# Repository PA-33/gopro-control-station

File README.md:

# GoPro Control Station

A complete remote control station for a GoPro Hero camera.

The system combines a two-axis motorised mount (so the camera can be aimed
without touching it) with full remote control of the camera itself
(shutter, mode, gallery, live HDMI preview). Everything is driven by a
single ESP32-S3 board running closed-loop FOC for the motors, BLE for
the camera commands, and an HTTPS web server for the user interface.

## Features

- Two-axis motorised mount with absolute angular position
- Magnetic encoders for accurate, drift-free positioning
- Soft-limits with automatic end-stop calibration
- Stall protection with auto-recovery (re-centres the motor on re-enable)
- BLE control of the GoPro (shutter, mode, sleep, keep-alive)
- Wi-Fi proxy to the GoPro REST API (gallery, thumbnails, downloads)
- Browser-based live HDMI preview via a USB-C capture card
- Self-signed HTTPS server with embedded certificate
- Persistent configuration and calibration in NVS
- Status LED strip for camera, motors, recording state and battery

The user interacts with the system through two parallel channels:

- **Physical panel** — five buttons (M1+, M1-, M2+, M2-, shutter) and a
  7-LED status strip.
- **Web interface** — served on the station's own Wi-Fi access point:
  control, gallery, live HDMI preview and configuration in a
  mobile-friendly UI.

## Repository layout

```
gopro-control-station/
├── platformio.ini              PlatformIO build configuration
├── README.md
├── LICENSE
│
├── src/                        Firmware sources (Arduino + ESP-IDF)
│   ├── bridge_main.cpp         setup() / loop() / status LEDs
│   ├── bridge_foc.cpp/.h       motor control, buttons, calibration
│   ├── bridge_current.cpp/.h   current sensing + stall detection
│   ├── bridge_ble.cpp/.h       NimBLE client (OpenGoPro)
│   ├── bridge_wifi.cpp/.h      Wi-Fi AP + STA + watchdog
│   ├── bridge_https.cpp/.h     TLS web server + REST proxy
│   ├── bridge_server.cpp/.h    plain HTTP (cert download only)
│   ├── bridge_config.cpp/.h    persistent configuration (NVS)
│   ├── bridge_led.h            LED constants
│   └── ssl_cert.h              embedded TLS certificate (auto-generated)
│
├── data/
│   └── index.html              single-page web UI (served from LittleFS)
│
├── certs/                      TLS certificate + regeneration toolchain
│   ├── bridge_cert.pem
│   ├── bridge_key.pem
│   ├── openssl.cnf
│   ├── generate.bat            Windows: regenerate cert + key + header
│   └── make_header.py          convert PEM into src/ssl_cert.h
│
├── hardware/
│   ├── cad/
│   │   ├── source/             CAD source files
│   │   └── exports/            exported 3D-printable files
│   └── kicad/
│       ├── gimbal_driver_board/ electrical schematic + PCB sources
│       └── exports/            generated manufacturing files
│
└── docs/
    ├── user_manual.pdf           end-user manual
    └── Mode_d_emploi.pdf         end-user manual (French)
```

## Quick start

### 1. Build and flash the firmware

```bash
# Firmware
pio run -e esp32-s3-bridge -t upload

# Web UI (LittleFS image)
pio run -e esp32-s3-bridge -t uploadfs

# Watch the boot log
pio device monitor -e esp32-s3-bridge
```

A clean first boot prints, in order: PCF8574 ready, FOC init OK x2,
Wi-Fi AP up, BLE connected to the camera, HTTPS server started, Wi-Fi
STA connected to the GoPro. See `docs/repport.tex` §5.5 for the
reference serial log.

### 2. Connect

1. Join the Wi-Fi network `GoPro-Bridge` (default password `gopro1234`).
2. Open `https://192.168.4.1` in a browser.
3. Accept the security warning, or download the certificate from the
   *Config* tab and install it to make the warning go away.

### 3. Adapt to your own GoPro

No source edit is required. After the first boot, go to the *Config* tab
in the web UI, replace the GoPro Wi-Fi SSID and password with the ones
printed on your camera (*Connections / Connect Device / GoPro App*),
*Save*, and reboot.

## Documentation

- **`docs/mode_emploi.tex`** — end-user manual (French). Buttons, LEDs,
  web interface, calibration procedure.
- **`hardware/cad/`** — CAD sources and exports for the mechanical
  parts. Print settings and assembly order are documented in §3 of the
  report.
- **`hardware/kicad/`** — full electrical schematic and PCB project. The pin
  assignments are also reproduced in §4 of the report and are
  hard-coded in the firmware (see `src/bridge_foc.cpp`).

## Regenerating the TLS certificate

The repository ships with a self-signed development certificate that
works out of the box. For any deployment where the local network is not
trusted, regenerate it:

```bash
cd certs
generate.bat            # Windows
# POSIX equivalent: see docs/repport.tex Appendix D
```

Then re-flash the firmware. Every client that already trusted the
previous certificate has to install the new one (web UI, *Config* tab).

## Hardware overview

- **MCU**: ESP32-S3 (`esp32-s3-devkitc-1`), 8 MB flash, no PSRAM.
- **Motors**: 2x BLDC (11 pole pairs), each driven by a DRV8313.
- **Encoders**: 2x AS5048A magnetic absolute encoders (SPI / HSPI bus).
- **Buttons**: 5x momentary, multiplexed through a PCF8574T (I2C).
- **Current sense**: 2x INA180A1 with 50 mOhm shunts, read on ADC2.
- **Indicators**: WS2815 strip, 7 LEDs.
- **Camera**: GoPro Hero (any model compatible with the OpenGoPro BLE
  specification) with the official Media Mod for HDMI output.
- **HDMI capture**: any UVC-class USB-C card (UGREEN 15389 is
  auto-selected by the web UI).

## License

This project is released under the [MIT License](LICENSE). You can use,
modify and redistribute it freely, including for commercial purposes,
provided that the copyright notice and the license text are kept.

## Acknowledgements

Built on top of [SimpleFOC](https://docs.simplefoc.com/),
[NimBLE-Arduino](https://github.com/h2zero/NimBLE-Arduino),
[ESPAsyncWebServer](https://github.com/mathieucarbou/ESPAsyncWebServer),
and the [pioarduino fork](https://github.com/pioarduino/platform-espressif32)
of `platform-espressif32`. Camera control follows the
[OpenGoPro](https://gopro.github.io/OpenGoPro/) specification.

## Context

This project was developed by Pierre Adamini and Florian Klein as part of
the Assistive Technology Challenge at EPFL (2026).

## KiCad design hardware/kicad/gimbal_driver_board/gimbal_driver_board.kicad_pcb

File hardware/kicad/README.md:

# KiCad project

Put the full KiCad source project here:

- `*.kicad_pro`
- `*.kicad_sch`
- `*.kicad_pcb`

Optional, only if you create local libraries later:

- `symbols/` for custom symbol libraries
- `footprints/` for custom footprint libraries

Use `exports/` for generated outputs only:

- Gerbers
- drill files
- PDF schematics
- BOM / pick-and-place files

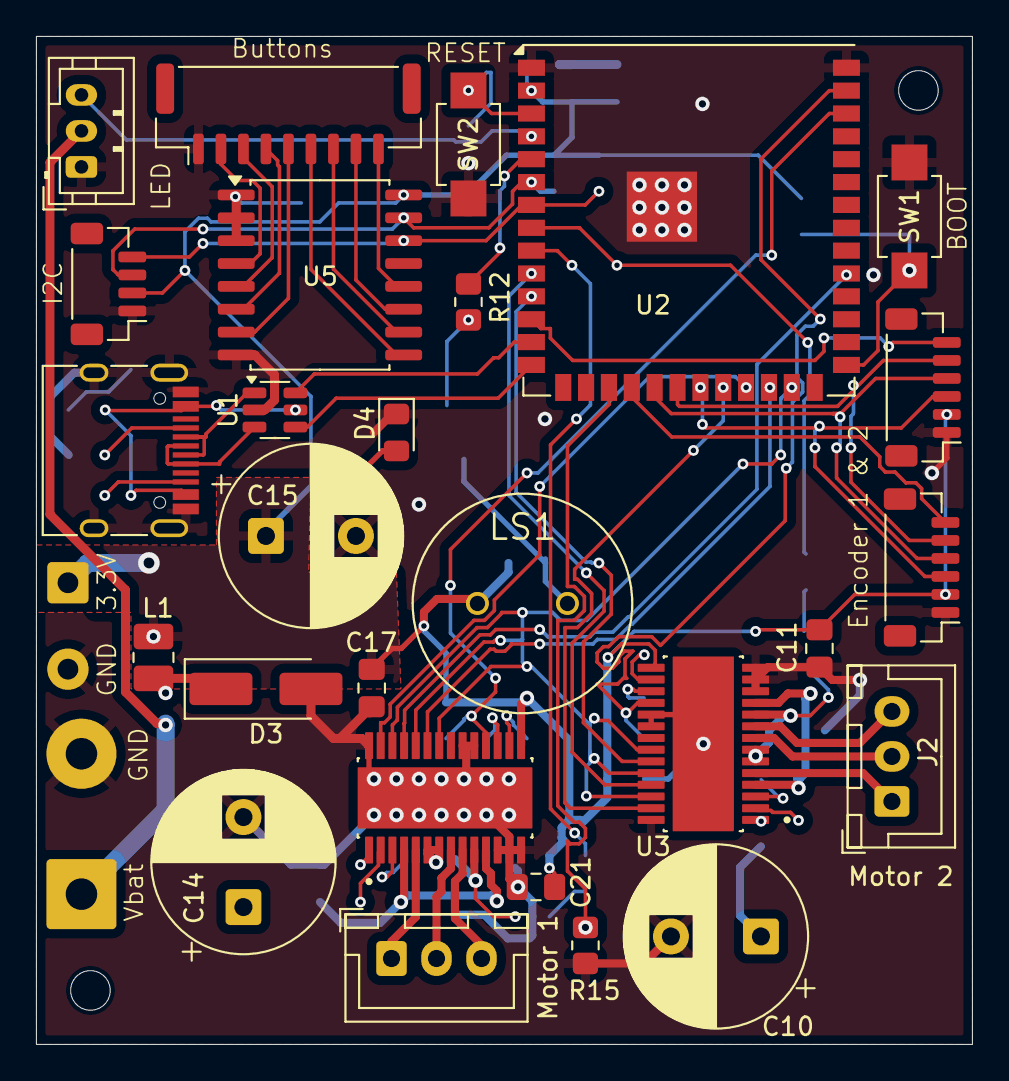
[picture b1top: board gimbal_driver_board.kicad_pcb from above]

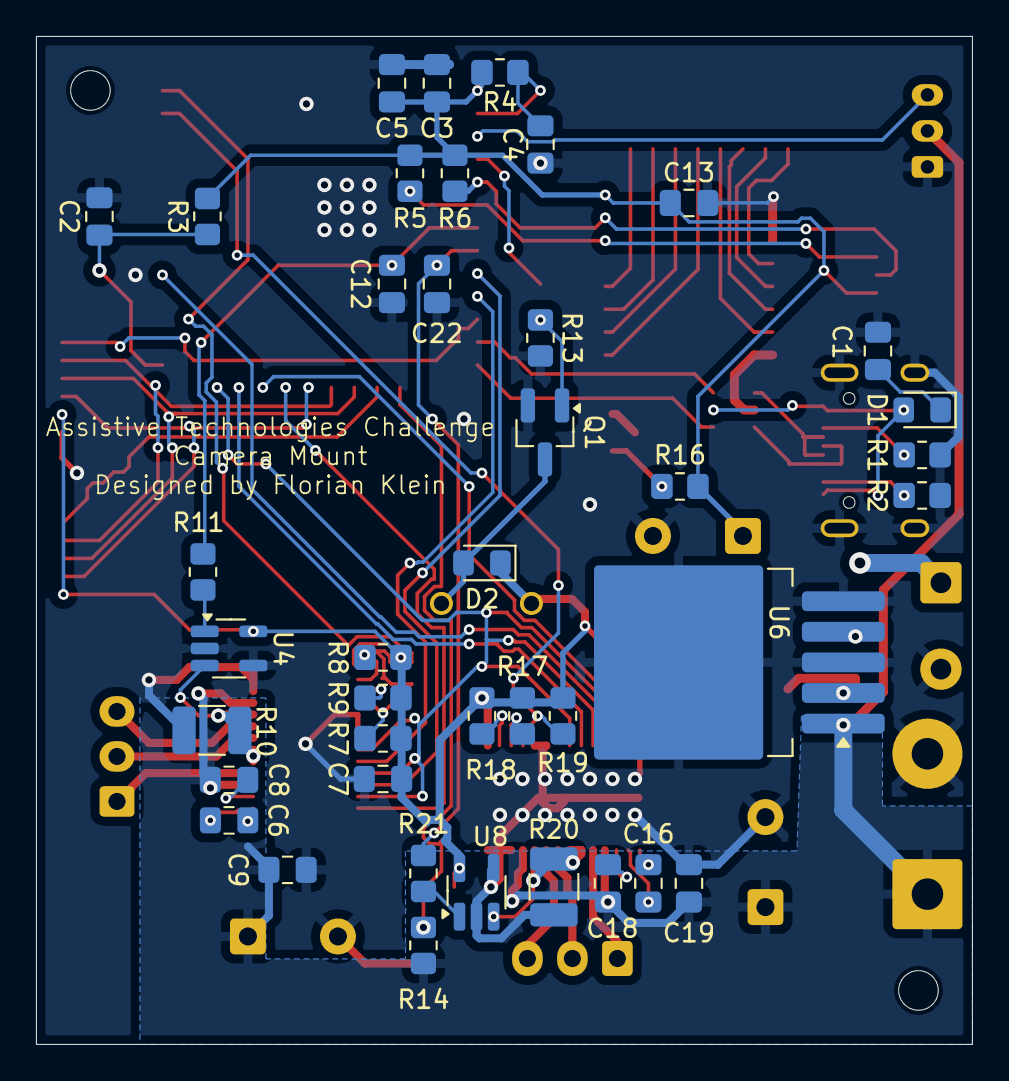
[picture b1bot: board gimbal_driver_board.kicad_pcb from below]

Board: 2 copper layers, 52.0 x 56.0 mm, 71 parts (40 on the bottom side), 66 nets.

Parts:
C1, C3: 10uF; C_0805_2012Metric_Pad1.18x1.45mm_HandSolder
C2, C4, C5, C8, C9, C11, C12, C13, C18, C19, C21, C22: 100nF; C_0805_2012Metric_Pad1.18x1.45mm_HandSolder
C6, C16: 10nF; C_0805_2012Metric_Pad1.18x1.45mm_HandSolder
C7, C17: 470nF; C_0805_2012Metric_Pad1.18x1.45mm_HandSolder
C10: 100uF; CP_Radial_D10.0mm_P5.00mm
C14, C15: 470uF; CP_Radial_D10.0mm_P5.00mm
D1: 1N5819HW-7-F; LED_0805_2012Metric_Pad1.15x1.40mm_HandSolder
D2: 1N5819WS; LED_0805_2012Metric_Pad1.15x1.40mm_HandSolder
D3: SS34; D_SMA_Handsoldering
D4: LED; LED_0805_2012Metric_Pad1.15x1.40mm_HandSolder
H1, H2: MountingHole; MountingHole_2.2mm_M2
J1: USB_C_Receptacle_USB2.0_16P; USB_C_Receptacle_HRO_TYPE-C-31-M-12
J2, J10: Motor; JST_XH_B3B-XH-A_1x03_P2.50mm_Vertical
J3: Encoder1; JST_SH_BM06B-SRSS-TB_1x06-1MP_P1.00mm_Vertical
J4: Conn_01x09_Socket; JST_GH_BM09B-GHS-TBT_1x09-1MP_P1.25mm_Vertical
J5: Encoder2; JST_SH_BM06B-SRSS-TB_1x06-1MP_P1.00mm_Vertical
J6: I2C; JST_SH_BM04B-SRSS-TB_1x04-1MP_P1.00mm_Vertical
J7: LED; JST_PH_B3B-PH-K_1x03_P2.00mm_Vertical
J8: Bat in; SolderWire-1sqmm_1x02_P7.8mm_D1.4mm_OD3.9mm
J9: 3v3 out; SolderWire-0.5sqmm_1x02_P4.8mm_D0.9mm_OD2.3mm
L1: 33uH; L_1008_2520Metric_Pad1.43x2.20mm_HandSolder
LS1: PS1240P02BT; XDCR_PS1240P02BT
Q1: AO3400A; SOT-23_Handsoldering
R1, R2: 5k1; R_0805_2012Metric_Pad1.20x1.40mm_HandSolder
R3, R4, R5, R6, R7, R8, R9, R11, R13, R17, R18, R19, R21: 10k; R_0805_2012Metric_Pad1.20x1.40mm_HandSolder
R10, R20: 0.05; R_1210_3225Metric_Pad1.30x2.65mm_HandSolder
R12: 100; R_0805_2012Metric_Pad1.20x1.40mm_HandSolder
R14, R15: R; R_0805_2012Metric_Pad1.20x1.40mm_HandSolder
R16: 1k; R_0805_2012Metric_Pad1.20x1.40mm_HandSolder
SW1, SW2: SW_MEC_5G; bouton_smd_kit_botanique
U1: USBLC6-2SC6; SOT-23-6
U2: ESP32-S3-WROOM-1; ESP32-S3-WROOM-1_homemade
U3, U7: DRV8313PWP; SOP65P640X120-29N
U4, U8: INA180A1; SOT-23-5_HandSoldering
U5: PCF8574T; SOIC-16W_7.5x10.3mm_P1.27mm
U6: LM2596S-3.3; TO-263-5_TabPin3

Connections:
1IN1: U2.22 (GPIO14/TOUCH14/ADC2_CH3/FSPIWP/FSPIDQS/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), U3.27 (IN1)
1IN2: U2.10 (GPIO17/U1TXD/ADC2_CH6), U3.25 (IN2)
1IN3: U2.11 (GPIO18/U1RXD/ADC2_CH7/CLK_OUT3), U3.23 (IN3)
2IN1: U2.23 (GPIO21), U7.27 (IN1)
2IN2: U2.31 (GPIO38/FSPIWP/SUBSPIWP), U7.25 (IN2)
2IN3: U2.24 (GPIO47/SPICLK_P/SUBSPICLK_P_DIFF), U7.23 (IN3)
+3.3V: C3.1, C5.1, C7.1, C11.1, C13.1, C15.1, C17.1, C21.1, D2.1 (K), J3.2, J5.2, J6.2, J9.1, L1.2, LS1.1, R3.2, R4.2, R5.1, R6.1, R7.1, R8.1, R9.2, R16.1, R17.1, R18.1, R19.2, U2.2 (3V3), U3.15 (V3P3), U4.5 (V+), U5.16 (VDD), U6.4 (FB), U7.15 (V3P3), U8.5 (V+)
ADC_bat: R14.2, R15.1, U2.17 (GPIO9/TOUCH9/ADC1_CH8/FSPIHD/SUBSPIHD)
Button0: J4.2, U5.4 (P0)
Button1: J4.3, U5.5 (P1)
Button2: J4.4, U5.6 (P2)
Button3: J4.5, U5.7 (P3)
Button4: J4.6, U5.9 (P4)
Button5: J4.7, U5.10 (P5)
Button6: J4.8, U5.11 (P6)
Button7: J4.9, U5.12 (P7)
Buzzer: R12.1, U2.5 (GPIO5/TOUCH5/ADC1_CH4)
CHIP_PU: C4.1, R4.1, SW2.3 (B), SW2.4 (B), U2.3 (EN)
CS1: J3.6, U2.18 (GPIO10/TOUCH10/ADC1_CH9/FSPICS0/FSPIIO4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)
CS2: J5.6, U2.12 (GPIO8/TOUCH8/ADC1_CH7/SUBSPICS1)
D+: U1.4 (I/O2), U2.14 (GPIO20/U1CTS/ADC2_CH9/CLK_OUT1/USB_D+)
D-: U1.6 (I/O1), U2.13 (GPIO19/U1RTS/ADC2_CH8/CLK_OUT2/USB_D-)
EN: U2.25 (GPIO48/SPICLK_N/SUBSPICLK_N_DIFF), U3.22 (EN3), U3.24 (EN2), U3.26 (EN1), U7.22 (EN3), U7.24 (EN2), U7.26 (EN1)
GND: C1.2, C2.2, C3.2, C4.2, C5.2, C7.2, C9.2, C10.2, C11.2, C12.2, C13.2, C14.2, C15.2, C17.2, C19.2, C21.2, C22.2, D3.2 (A), D4.1 (K), J1.A1 (GND), J1.A12 (GND), J1.B1 (GND), J1.B12 (GND), J1.S1 (SHIELD), J3.1, J4.1, J5.1, J6.1, J7.1, J8.2, J9.2, Q1.2 (S), R1.2, R2.2, R10.2, R13.2, R15.2, R20.2, SW1.1 (A), SW1.2 (A), SW2.1 (A), SW2.2 (A), U1.2 (GND), U2.1 (GND), U2.40 (GND), U2.41 (GND), U3.12 (COMPP), U3.13 (COMPN), U3.14 (GND), U3.19 (~COMPO), U3.20 (GND), U3.28 (GND), U3.29 (EXP), U4.2 (GND), U4.4 (-), U5.1 (A0), U5.2 (A1), U5.3 (A2), U5.8 (GND), U6.3 (GND), U6.5 (~ON/OFF), U7.12 (COMPP), U7.13 (COMPN), U7.14 (GND), U7.19 (~COMPO), U7.20 (GND), U7.28 (GND), U7.29 (EXP), U8.2 (GND), U8.4 (-)
GPIO0: C2.1, R3.1, SW1.3 (B), SW1.4 (B), U2.27 (GPIO0/BOOT)
I1: C12.1, R11.2, U2.8 (GPIO15/U0RTS/ADC2_CH4/XTAL_32K_P)
I2: C22.1, R21.2, U2.9 (GPIO16/U0CTS/ADC2_CH5/XTAL_32K_N)
LED: J7.3, U2.4 (GPIO4/TOUCH4/ADC1_CH3)
MISO: J3.3, J5.3, U2.21 (GPIO13/TOUCH13/ADC2_CH2/FSPIQ/FSPIIO7/S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)
MOSI: J3.4, J5.4, U2.19 (GPIO11/TOUCH11/ADC2_CH0/FSPID/FSPIIO5/S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)
unnamed: D1.2 (A), J1.A4 (VBUS), J1.A9 (VBUS), J1.B4 (VBUS), J1.B9 (VBUS), U1.5 (VBUS)
unnamed: C1.1, D1.1 (K)
unnamed: D2.2 (A), LS1.2, Q1.3 (D)
unnamed: D3.1 (K), L1.1, U6.2 (OUT)
unnamed: D4.2 (A), R16.2
unnamed: J1.A5 (CC1), R1.1
unnamed: J1.B5 (CC2), R2.1
unnamed: J1.A6 (D+), J1.B6 (D+), U1.3 (I/O2)
unnamed: J1.A7 (D-), J1.B7 (D-), U1.1 (I/O1)
unnamed: J2.1, U3.5 (OUT1)
unnamed: J2.2, U3.8 (OUT2)
unnamed: J2.3, U3.9 (OUT3)
unnamed: J10.1, U7.5 (OUT1)
unnamed: J10.2, U7.8 (OUT2)
unnamed: J10.3, U7.9 (OUT3)
unnamed: Q1.1 (G), R12.2, R13.1
unnamed: R11.1, U4.1
unnamed: R21.1, U8.1
unnamed: C6.2, U3.2 (CPH)
unnamed: C6.1, U3.1 (CPL)
unnamed: R10.1, U3.6 (PGND1), U3.7 (PGND2), U3.10 (PGND3), U4.3 (+)
unnamed: C8.1, U3.3 (VCP)
unnamed: R8.2, U3.16 (~RESET)
unnamed: R7.2, U3.17 (~SLEEP)
unnamed: C16.2, U7.2 (CPH)
unnamed: C16.1, U7.1 (CPL)
unnamed: R20.1, U7.6 (PGND1), U7.7 (PGND2), U7.10 (PGND3), U8.3 (+)
unnamed: C18.1, U7.3 (VCP)
unnamed: R18.2, U7.16 (~RESET)
unnamed: R17.2, U7.17 (~SLEEP)
SCL: J6.4, R5.2, U2.7 (GPIO7/TOUCH7/ADC1_CH6), U5.14 (SCL)
SCLK: J3.5, J5.5, U2.20 (GPIO12/TOUCH12/ADC2_CH1/FSPICLK/FSPIIO6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)
SDA: J6.3, R6.2, U2.6 (GPIO6/TOUCH6/ADC1_CH5), U5.15 (SDA)
VCC: C8.2, C9.1, C10.1, C14.1, C18.2, C19.1, J7.2, J8.1, R14.1, U3.4 (VM), U3.11 (VM), U6.1 (VIN), U7.4 (VM), U7.11 (VM)
nFT1: R9.1, U2.39 (GPIO1/TOUCH1/ADC1_CH0), U3.18 (~FAULT)
nFT2: R19.1, U2.38 (GPIO2/TOUCH2/ADC1_CH1), U7.18 (~FAULT)

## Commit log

2026-06-04 mod readme
2026-06-05 add .h files fix: calibration stopping too early resulting of one motor not going back in its middle position
2026-06-05 added CAD and Kicad files and updated README
2026-06-05 added BOM
2026-06-05 add french and english user manual
2026-06-05 Update end-user manual file names in README
